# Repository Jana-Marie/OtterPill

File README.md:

# OtterPill

OtterPill is a 3$ STM32F072 devboard featuring USB 2.0 full-speed, a DFU Bootloader, a USB-PD Phy and Arduino nano alike pinout and size.

Changelog V1.2: BOM cost reduction by ~40%, PCB can be fully populated by JLCSMT, more efficient buck converter (PCB gets less warm at 20V), GND-hook for probing, Reset-Pin exposed as pad, power pads for 20V/5A

**How do I get an OtterPill?**

Via [tindie](https://www.tindie.com/products/jan_henrik/otterpill/) (if sold out DM via Twitter, I might have a few left ;))

## Building, Flashing and Frameworks

### Via Makefile and DFU (C, C++)

Or you can generate a basic firmware, with HAL init and Makefile, with CubeMX. The binary can then be build with make and flashed with dfu-utils. To enter DFU mode, press and hold the Button while plugging in power.

    $ make
    $ dfu-util -a 0 -s 0x08000000:leave -D build/firmware.bin

### Via Arduino

[You can build and flash the firmware via Arduino as described here.](https://github.com/stm32duino/Arduino_Core_STM32)

### Via PlatformIO

[https://gist.github.com/ansemjo/ab1c12f7c78abb140f7272501aff2a55](https://gist.github.com/ansemjo/ab1c12f7c78abb140f7272501aff2a55) Thank you [ansemjo](https://github.com/ansemjo) :3

### Via Nodate (野点) (C++, Ada)

[https://github.com/MayaPosch/Nodate](https://github.com/MayaPosch/Nodate)

### Rust

Thank you [@jamesmunns](https://github.com/jamesmunns)! :3

[https://github.com/jamesmunns/OtterPill-rs](https://github.com/jamesmunns/OtterPill-rs)

## Schematic

[HW v1.2/OtterPill.pdf](HW%20v1.2/OtterPill.pdf)

## Pinout

Pinout by [SarahhhhFoster](https://github.com/SarahhhhFoster) :)

## Examples and projects

### Blink example firmware

[Blink/](Blink/)

### STM workshop based on OtterPill

[https://github.com/Jana-Marie/hackerhotel-stm-workshop](https://github.com/Jana-Marie/hackerhotel-stm-workshop)

### USB-PD example firmware

This is a working USB-PD example using ChibiOS, a new voltage can be requested by pressing the Button.

[https://github.com/Jana-Marie/USB-PD-Firmware](https://github.com/Jana-Marie/USB-PD-Firmware)

### IBM dials retrofit

[https://github.com/Jana-Marie/IBM-dials-retrofit](https://github.com/Jana-Marie/IBM-dials-retrofit)

## Shields and addons

Most Arduino shields should be compatible.

#### [USB-to-CAN-adapter](https://github.com/Jana-Marie/OtterPill-CAN-Adapter)

## Todo for HW v1.3

 - [x] Replace U1 with ESDU5V0H4
 - [x] ~~Add a TVS Diode to VBUS (e.g. SJD12A22L01)~~ -> Added series resistor to reduce ringing
 - [ ] Remove R8, R9
 - [x] ~~Redraw the FUSB302B Symbol~~ -> forgot why, works great
 - [x] ~~Consider switching to STUSB4500 (Easier PD requesting, same price)~~ -> FUSB works great, no need to change
 - [x] Add VBUS ADC

## Special thanks

[@jamesmunns](https://github.com/jamesmunns) for creating the Rust examples.

[@MayaPosch](https://github.com/MayaPosch) for creating the Nodate framework and adding the OtterPill.

[@ansemjo](https://github.com/ansemjo) for creating a PlatformIO configuration.

[@SarahhhhFoster](https://github.com/SarahhhhFoster) for creating the awesome pinout diagram.

## Images

### Rev 1.2

### License

Copyright Jana Marie Hemsing 2027.

This source describes Open Hardware and is licensed under the CERN-OHL-S v2.

You may redistribute and modify this source and make products using it under
the terms of the CERN-OHL-S v2 (https://ohwr.org/cern_ohl_s_v2.txt).

This source is distributed WITHOUT ANY EXPRESS OR IMPLIED WARRANTY,
INCLUDING OF MERCHANTABILITY, SATISFACTORY QUALITY AND FITNESS FOR A
PARTICULAR PURPOSE. Please see the CERN-OHL-S v2 for applicable conditions.

Source location: https://github.com/Jana-Marie/OtterPill

As per CERN-OHL-S v2 section 4, should You produce hardware based on this
source, You must where practicable maintain the Source Location visible
on the external case of the Gizmo or other products you make using this
source.

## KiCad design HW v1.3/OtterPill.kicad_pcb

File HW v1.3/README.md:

# OtterPill

Hardware rev 1.3 not tested, gerber are broken.

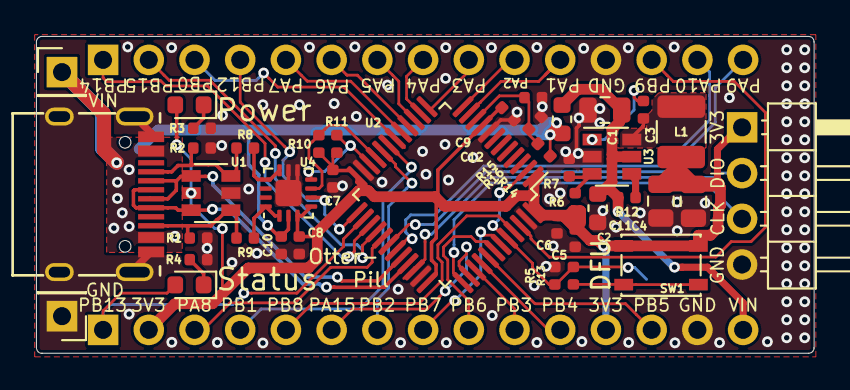
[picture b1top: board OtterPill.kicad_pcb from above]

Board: 2 copper layers, 43.2 x 17.6 mm, 43 parts (1 on the bottom side), 48 nets.

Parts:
C1, C4, C11: 10u 25V; C_0805_2012Metric
C2: 100n 50V; C_0603_1608Metric
C3, C5, C6, C7, C8, C9, C10, C12: 100n 50V; C_0402_1005Metric
D1: LED RED; LED_0603_1608Metric
D2: LED GREEN; LED_0603_1608Metric
J1: USB-c; USB-C 16Pin
J2: VBUS; PinHeader_1x01_P2.54mm_Vertical
J3: 1; PinHeader_1x15_P2.54mm_Vertical
J4: 2; PinHeader_1x15_P2.54mm_Vertical
J5: SWD; PinHeader_1x04_P2.54mm_Horizontal
J6: GND; PinHeader_1x01_P2.54mm_Vertical
J7: PAD; TestPoint_Pad_1.0x1.0mm
L1: 4u7; L_1210_3225Metric
R1, R2: DNP; R_0402_1005Metric
R3, R4, R5, R10, R11: 3k3; R_0402_1005Metric
R6, R12, R14: 100k; R_0402_1005Metric
R7, R15: 22k; R_0402_1005Metric
R8, R9: 0; R_0402_1005Metric
R13: 100; R_0402_1005Metric
R16: 1; R_0603_1608Metric
SW1: DFU; SW_SPST_PTS810
U1: USBLC6-4; SOT-23-6
U2: STM32F072C8Tx; LQFP-48_7x7mm_P0.5mm
U3: SY8201; SOT-23-6
U4: FUSB302BMPX; WQFN-14-1EP_2.5x2.5mm_P0.5mm_EP1.45x1.45mm

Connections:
+3V3: C4.1, C5.1, C6.1, C7.1, C8.1, C9.1, C11.1, D1.2, J4.2, J4.12, J5.1, L1.2, R6.1, R10.1, R11.1, SW1.2, U1.5, U2.1, U2.9, U2.24, U2.36, U2.48, U4.3, U4.4
CC1: J1.A5, R2.2, R8.1, U1.3
CC2: J1.B5, R1.2, R9.1, U1.1
GND: C1.2, C2.2, C4.2, C5.2, C6.2, C7.2, C8.2, C9.2, C10.2, C11.2, C12.2, J1.A1, J1.B1, J1.S1, J3.12, J4.14, J5.4, J6.1, R1.1, R2.1, R3.2, R4.2, R5.2, R7.2, R15.2, U1.2, U2.8, U2.23, U2.35, U2.47, U3.2, U4.8, U4.9, U4.15
INT_N: J3.4, U2.25, U4.5
unnamed: C3.1, U3.1
unnamed: C3.2, L1.1, U3.6
unnamed: D1.1, R3.1
unnamed: D2.1, R4.1
unnamed: J7.1, R5.1, R13.2, U2.2, U2.44
unnamed: R6.2, R7.1, U3.3
unnamed: R8.2, U4.10, U4.11
unnamed: R9.2, U4.1, U4.14
unnamed: R12.2, U3.4
unnamed: R13.1, SW1.1
PA0: C12.1, R14.2, R15.1, U2.10
PA1: J3.11, U2.11
PA2: J3.10, U2.12
PA3: J3.9, U2.13
PA4: J3.8, U2.14
PA5: J3.7, U2.15
PA6: J3.6, U2.16
PA7: J3.5, U2.17
PA8: J4.3, U2.29
PA9: J3.15, U2.30
PA10: J3.14, U2.31
PA15: J4.6, U2.38
PB0: J3.3, U2.18
PB1: J4.4, U2.19
PB2: J4.7, U2.20
PB3: J4.10, U2.39
PB4: J4.11, U2.40
PB5: J4.13, U2.41
PB6: J4.9, U2.42
PB7: J4.8, U2.43
PB8: J4.5, U2.45
PB9: J3.13, U2.46
PB13: D2.2, J4.1, U2.26
PB14: J3.1, U2.27
PB15: J3.2, U2.28
SCL: R10.2, U2.21, U4.6
SDA: R11.2, U2.22, U4.7
SWCLK: J5.3, U2.37
SWDIO: J5.2, U2.34
USB_N: J1.A7, J1.B7, U1.4, U2.32
USB_P: J1.A6, J1.B6, U1.6, U2.33
VBUS: C10.1, J1.A4, J1.B4, J2.1, R14.1, R16.1, U4.2
VIN: C1.1, C2.1, J4.15, R12.1, R16.2, U3.5

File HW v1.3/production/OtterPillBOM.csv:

Comment,Designator,Footprint,LCSC
10u 25V,"C1,C4,C11",Capacitor_SMD:C_0805_2012Metric,C15850
100n 50V,C2,Capacitor_SMD:C_0603_1608Metric,C14663
100n 50V,"C3,C5,C6,C7,C8,C9,C10,C12",Capacitor_SMD:C_0402_1005Metric,C1525
LED RED,D1,LED_SMD:LED_0603_1608Metric,C2286
LED GREEN,D2,LED_SMD:LED_0603_1608Metric,C72043
USB-c,J1,otter:USB-C 16Pin,
4u7,L1,Inductor_SMD:L_1210_3225Metric,C86070
DNP,"R1,R2",Resistor_SMD:R_0402_1005Metric,dnp
100,R13,Resistor_SMD:R_0402_1005Metric,C25076
1,R16,Resistor_SMD:R_0603_1608Metric,C22936
3k3,"R5,R3,R4,R10,R11",Resistor_SMD:R_0402_1005Metric,C25890
100k,"R6,R12,R14",Resistor_SMD:R_0402_1005Metric,C25741
22k,"R7,R15",Resistor_SMD:R_0402_1005Metric,C25768
0,"R8,R9",Resistor_SMD:R_0402_1005Metric,C17168
DFU,SW1,Button_Switch_SMD:SW_SPST_PTS810,
USBLC6-4,U1,Package_TO_SOT_SMD:SOT-23-6,C111212
STM32F072C8Tx,U2,Package_QFP:LQFP-48_7x7mm_P0.5mm,C80488
SY8201,U3,Package_TO_SOT_SMD:SOT-23-6,C108052
FUSB302BMPX,U4,Package_DFN_QFN:WQFN-14-1EP_2.5x2.5mm_P0.5mm_EP1.45x1.45mm,C132291

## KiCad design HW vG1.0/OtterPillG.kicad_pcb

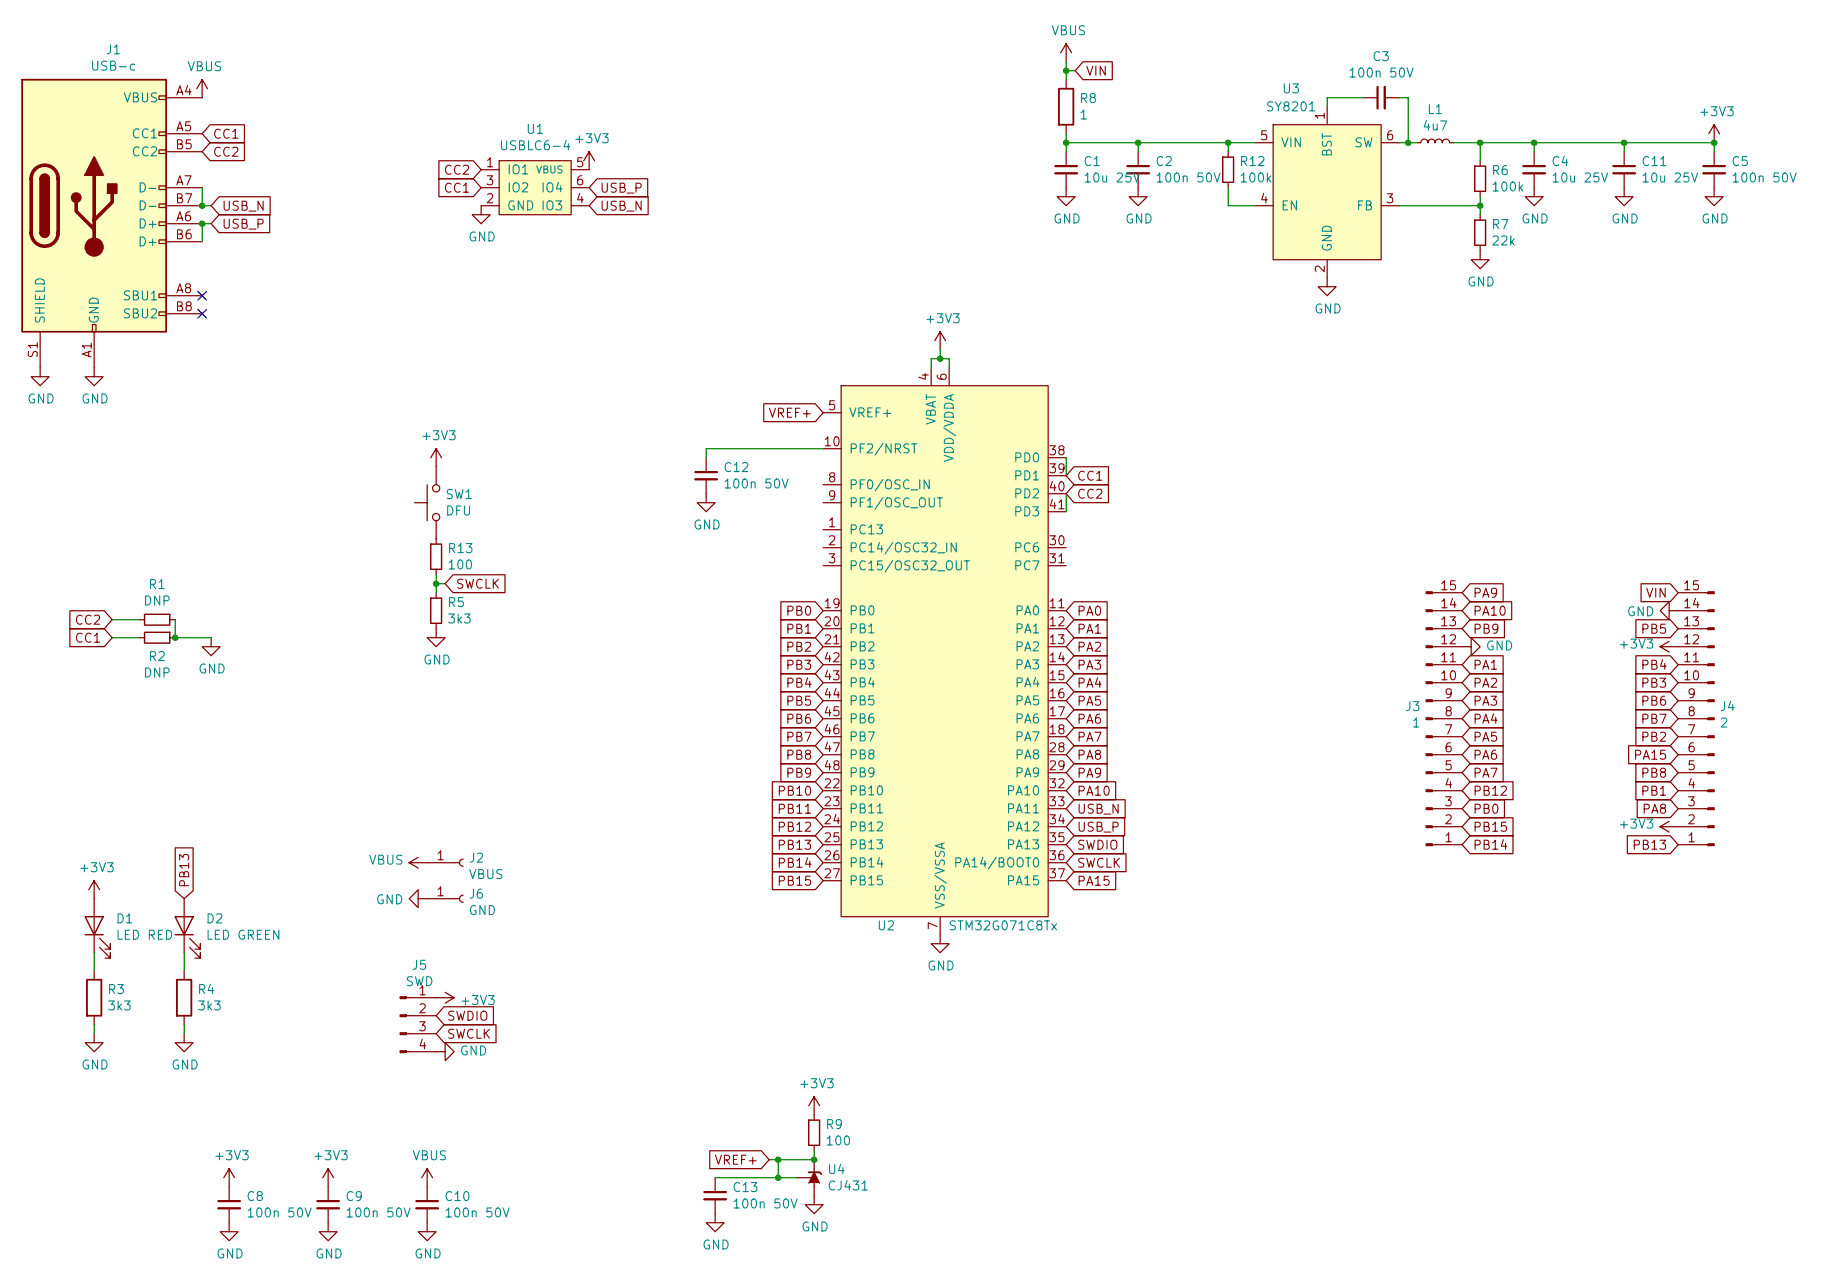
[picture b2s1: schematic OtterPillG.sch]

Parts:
C1, C4, C11: 10u 25V; C_0805; LCSC C15850
C2: 100n 50V; C_0603
C3, C5, C8, C9, C10, C12, C13: 100n 50V; C_0402
D1: LED RED; LED_0603_1608Metric
D2: LED GREEN; LED_0603_1608Metric
J1: USB-c; USB-C 16Pin
J2: VBUS; PinHeader_1x01_P2.54mm_Vertical
J3: 1; PinHeader_1x15_P2.54mm_Vertical
J4: 2; PinHeader_1x15_P2.54mm_Vertical
J5: SWD; PinHeader_1x04_P2.54mm_Horizontal
J6: GND; PinHeader_1x01_P2.54mm_Vertical
L1: 4u7; L_1210_3225Metric; LCSC C86070
R1, R2: DNP; R_0402
R3, R4, R5: 3k3; R_0402
R6, R12: 100k; R_0402
R7: 22k; R_0402
R8: 1; R_0805
R9, R13: 100; R_0402
SW1: DFU; SW_SPST_PTS810
U1: USBLC6-4; SOT-23-6
U2: STM32G071C8Tx; TQFP-48_7x7mm_P0.5mm
U3: SY8201; SOT-23-6
U4: CJ431; SOT-23

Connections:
+3V3: C4.1, C5.1, C8.1, C9.1, C11.1, D1.2 (A), J4.2, J4.12, J5.1, L1.2, R6.1, R9.1, SW1.2, U1.5 (VBUS), U2.4 (VBAT), U2.6 (VDD/VDDA)
CC1: J1.A5 (CC1), R2.2, U1.3 (IO2), U2.38 (PD0), U2.39 (PD1)
CC2: J1.B5 (CC2), R1.2, U1.1 (IO1), U2.40 (PD2), U2.41 (PD3)
GND: C1.2, C2.2, C4.2, C5.2, C8.2, C9.2, C10.2, C11.2, C12.2, C13.2, J1.A1 (GND), J1.A12 (GND), J1.B1 (GND), J1.B12 (GND), J1.S1 (SHIELD), J3.12, J4.14, J5.4, J6.1, R1.1, R2.1, R3.2, R4.2, R5.2, R7.2, U1.2 (GND), U2.7 (VSS/VSSA), U3.2 (GND), U4.3 (A)
unnamed: C1.1, C2.1, R8.2, R12.1, U3.5 (VIN)
unnamed: C3.1, U3.1 (BST)
unnamed: C3.2, L1.1, U3.6 (SW)
unnamed: C12.1, U2.10 (PF2/NRST)
unnamed: D1.1 (K), R3.1
unnamed: D2.1 (K), R4.1
unnamed: R6.2, R7.1, U3.3 (FB)
unnamed: R12.2, U3.4 (EN)
unnamed: R13.1, SW1.1
PA0: U2.11 (PA0)
PA1: J3.11, U2.12 (PA1)
PA2: J3.10, U2.13 (PA2)
PA3: J3.9, U2.14 (PA3)
PA4: J3.8, U2.15 (PA4)
PA5: J3.7, U2.16 (PA5)
PA6: J3.6, U2.17 (PA6)
PA7: J3.5, U2.18 (PA7)
PA8: J4.3, U2.28 (PA8)
PA9: J3.15, U2.29 (PA9)
PA10: J3.14, U2.32 (PA10)
PA15: J4.6, U2.37 (PA15)
PB0: J3.3, U2.19 (PB0)
PB1: J4.4, U2.20 (PB1)
PB2: J4.7, U2.21 (PB2)
PB3: J4.10, U2.42 (PB3)
PB4: J4.11, U2.43 (PB4)
PB5: J4.13, U2.44 (PB5)
PB6: J4.9, U2.45 (PB6)
PB7: J4.8, U2.46 (PB7)
PB8: J4.5, U2.47 (PB8)
PB9: J3.13, U2.48 (PB9)
PB10: U2.22 (PB10)
PB11: U2.23 (PB11)
PB12: J3.4, U2.24 (PB12)
PB13: D2.2 (A), J4.1, U2.25 (PB13)
PB14: J3.1, U2.26 (PB14)
PB15: J3.2, U2.27 (PB15)
SWCLK: J5.3, R5.1, R13.2, U2.36 (PA14/BOOT0)
SWDIO: J5.2, U2.35 (PA13)
USB_N: J1.A7 (D-), J1.B7 (D-), U1.4 (IO3), U2.33 (PA11)
USB_P: J1.A6 (D+), J1.B6 (D+), U1.6 (IO4), U2.34 (PA12)
VIN: C10.1, J1.A4 (VBUS), J1.A9 (VBUS), J1.B4 (VBUS), J1.B9 (VBUS), J2.1, J4.15, R8.1
VREF+: C13.1, R9.2, U2.5 (VREF+), U4.1 (REF), U4.2 (K)

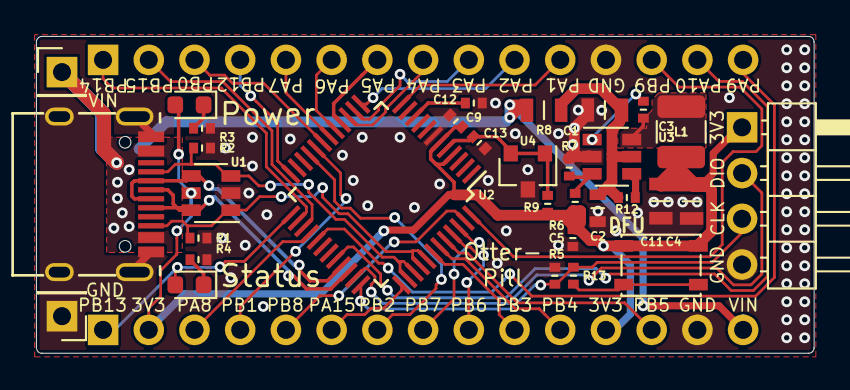
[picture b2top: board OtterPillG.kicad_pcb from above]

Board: 2 copper layers, 43.2 x 17.6 mm, 34 parts (0 on the bottom side), 44 nets.

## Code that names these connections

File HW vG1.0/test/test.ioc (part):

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Mcu.Name=STM32G071C(6-8-B)Tx
Mcu.Package=LQFP48
Mcu.UserName=STM32G071C8Tx
PA1.Mode=IN1
PA1.Signal=ADC1_IN1
PA13.Mode=Serial_Wire
PA13.Signal=SYS_SWDIO
PA14-BOOT0.Mode=Serial_Wire
PA14-BOOT0.Signal=SYS_SWCLK
PA2.Mode=Asynchronous
PA2.Signal=LPUART1_TX
PA3.Mode=Asynchronous
PA3.Signal=LPUART1_RX
PB13.Signal=GPIO_Output
PD0.Mode=Sink_AllSignals
PD0.Signal=UCPD2_CC1
PD1.Mode=EnableDeadBattery
PD1.Signal=UCPD2_DBCC1
PD2.Mode=Sink_AllSignals
PD2.Signal=UCPD2_CC2
PD3.Mode=EnableDeadBattery
PD3.Signal=UCPD2_DBCC2
RCC.HSE_VALUE=8000000
RCC.SYSCLKFreq_VALUE=64000000
RCC.SYSCLKSource=RCC_SYSCLKSOURCE_PLLCLK
board=custom

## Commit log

2019-05-05 added gitignore
2019-05-05 initital commit
2019-05-06 added gerber
2019-05-17 v1.2
2019-10-16 updated PCB and gerber
2019-10-16 updated images and README
2019-10-16 removed old images
2019-10-16 updated gerber
2019-10-16 removed old gerber
2019-10-18 added BOM
2019-10-18 Rename OtterPill.csv to OtterPill.tsv
2019-10-20 updated otterpill to V1.2
2019-10-23 added HW 1.1 files
2019-10-23 moved HW 1.2 files
2019-10-23 Fix kitspace.yaml
2019-10-24 updated V1.2
2019-11-17 finalized V1.2
2019-12-20 updated values
2019-12-20 added new images
2019-12-20 added pinout
2019-12-21 schematic cleanup
2019-12-21 added library
2019-12-21 added libraries
2019-12-21 removed autosave file
2019-12-21 fixed bom
2020-01-18 added blink example
2020-01-25 Add OtterPill v1.2 Schematic PDF
2020-02-02 Updating Readme Image
2020-03-28 added x4 production files
2020-03-28 added edgerails
2020-03-28 updated bom
2020-04-15 added boms
2020-04-15 fixed 100k
2020-04-22 added images
2020-09-14 added G072 version
2020-09-14 removed old files
2020-10-31 updated v1.3
2020-10-31 updated vG1.0
2020-10-31 added production files
2022-01-19 updated license
2023-01-04 added kicad files
2023-01-04 updated gitignore
2023-01-04 added silkscreen art
2023-01-04 added readme
2023-01-04 fixed schematic issue
